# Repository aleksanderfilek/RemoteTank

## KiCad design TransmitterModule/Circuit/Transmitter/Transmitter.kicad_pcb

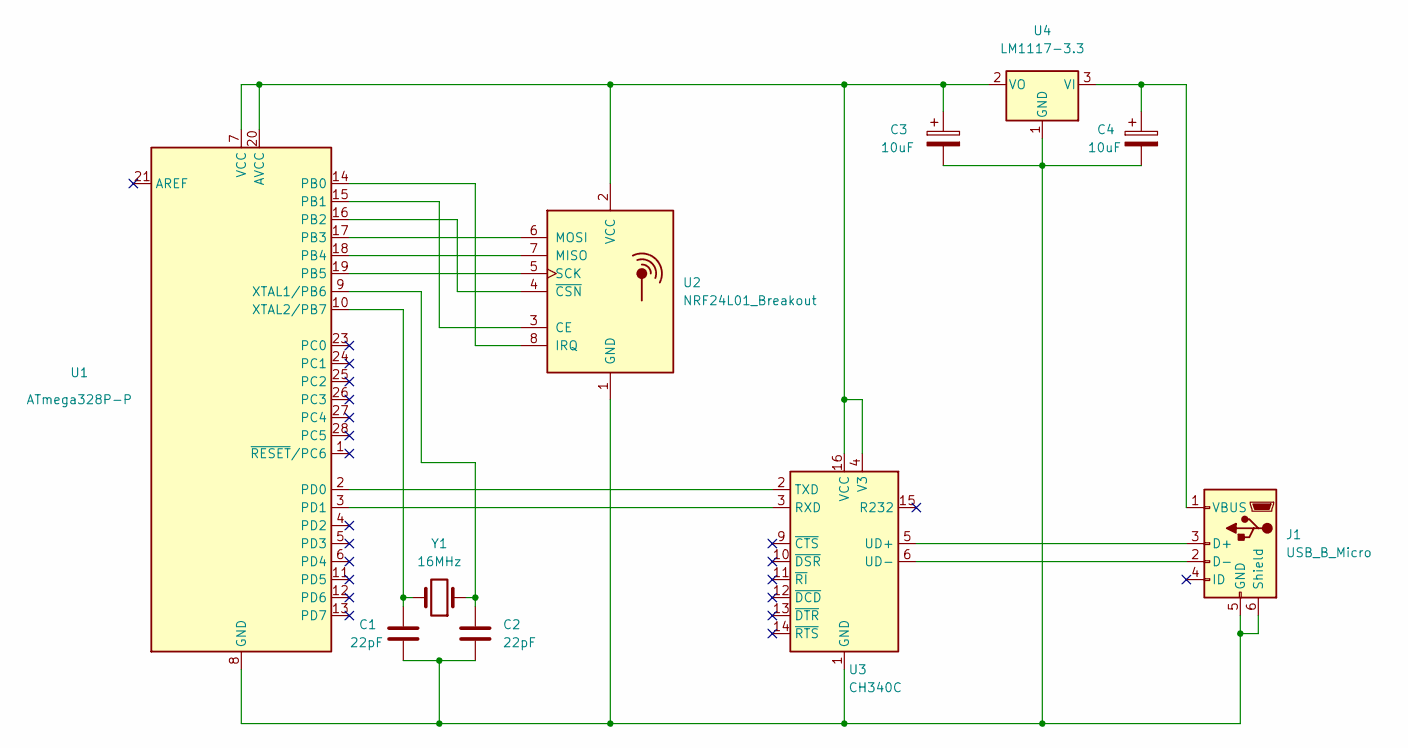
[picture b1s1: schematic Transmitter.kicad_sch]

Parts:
C1, C2: 22pF; C_Disc_D3.8mm_W2.6mm_P2.50mm
C3, C4: 10uF; CP_Radial_D4.0mm_P2.00mm
J1: USB_B_Micro; USB_Micro-AB_Molex_47590-0001
U1: ATmega328P-P; DIP-28_W7.62mm
U2: NRF24L01_Breakout; nRF24L01_Breakout
U3: CH340C; SOIC-16_3.9x9.9mm_P1.27mm
U4: LM1117-3.3; TO-252-2
Y1: 16MHz; Crystal_HC49-U_Vertical

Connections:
unnamed: C1.1, U1.10 (XTAL2/PB7), Y1.2
unnamed: C1.2, C2.2, C3.2, C4.2, J1.5 (GND), J1.6 (Shield), U1.8 (GND), U1.22 (GND), U2.1 (GND), U3.1 (GND), U4.1 (GND)
unnamed: C2.1, U1.9 (XTAL1/PB6), Y1.1
unnamed: C3.1, U1.7 (VCC), U1.20 (AVCC), U2.2 (VCC), U3.4 (V3), U3.16 (VCC), U4.2 (VO)
unnamed: C4.1, J1.1 (VBUS), U4.3 (VI)
unnamed: J1.2 (D-), U3.6 (UD-)
unnamed: J1.3 (D+), U3.5 (UD+)
unnamed: U1.2 (PD0), U3.2 (TXD)
unnamed: U1.3 (PD1), U3.3 (RXD)
unnamed: U1.14 (PB0), U2.8 (IRQ)
unnamed: U1.15 (PB1), U2.3 (CE)
unnamed: U1.16 (PB2), U2.4 (~CSN)
unnamed: U1.17 (PB3), U2.6 (MOSI)
unnamed: U1.18 (PB4), U2.7 (MISO)
unnamed: U1.19 (PB5), U2.5 (SCK)

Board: 2 copper layers, 10 parts (0 on the bottom side), 15 nets, no tracks yet.

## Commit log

2022-08-19 transmitter circuit
2022-08-28 code + documents
2022-11-07 nrf24 driver
2022-11-14 motor
2022-11-14 praca init
2022-11-16 transmiter circuit
2022-11-16 vehicle scheme
2022-11-22 rf24lib
2022-11-22 transmiter module code v1
2022-12-09 schematic
2022-12-28 app INIT
2022-12-28 transmiter audio update
2022-12-28 stabilizator update in circuits
2022-12-28 RVC library
2022-12-30 uart communication + command manager
2022-12-30 [App] communication + command managers
2023-01-08 speedrun
2023-01-10 app update
